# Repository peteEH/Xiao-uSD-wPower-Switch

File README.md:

# Xiao-uSD-wPower-Switch

You should definately purchase a pre-made Adafruit variant: https://www.adafruit.com/product/5683 --- if you don't need a power switch.
- free to select the right p-channel FET that is logic-level compatible, has lower RDSon for the SDcard rail
- hard to beat the Adafruit board for cost... but shipping to Canada is a killer!

ChatGPT Summary of the Schematic PDF:

The document provides a schematic for a microSD (uSD) card adapter with a power switch, specifically designed for use with Xiao or QT Py microcontrollers. It details the electrical components and their configurations, including capacitors, resistors, and a power MOSFET (Q1) for controlling power to the SD card. The schematic includes connections for power, ground, and various data lines (MOSI, MISO, SCLK, CS_N) necessary for SPI communication with the SD card. It also specifies the physical dimensions of the board and the placement of connectors and components, ensuring compatibility with the Xiao or QT Py form factor.

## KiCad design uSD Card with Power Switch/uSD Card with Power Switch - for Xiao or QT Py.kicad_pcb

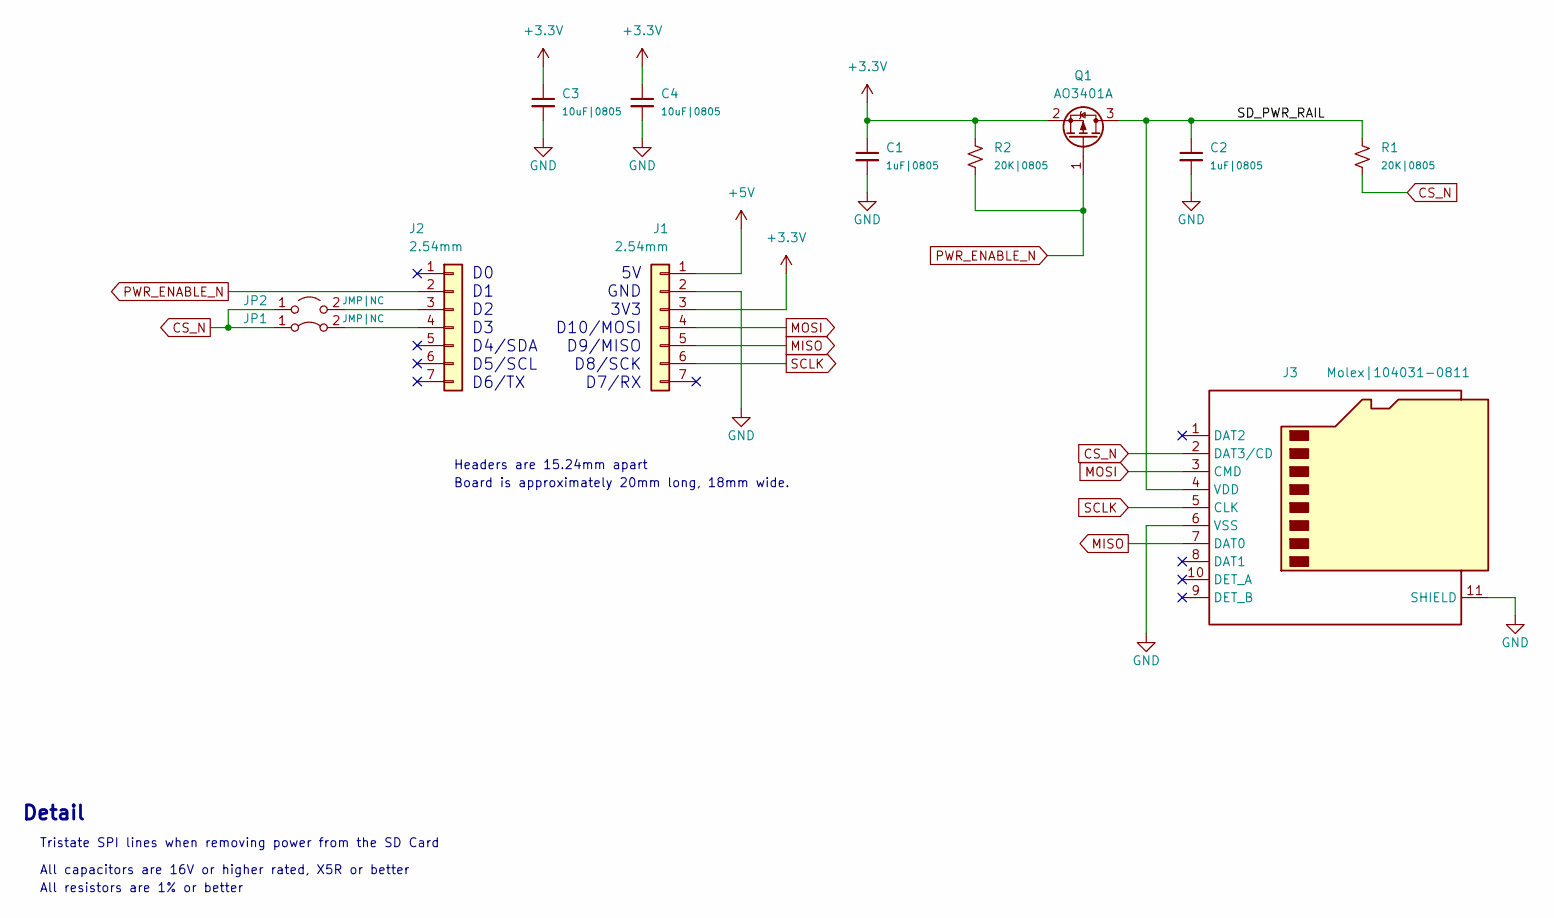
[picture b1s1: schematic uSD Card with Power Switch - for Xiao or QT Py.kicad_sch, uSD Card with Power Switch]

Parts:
C1, C2: 1uF|0805; C_0805_2012Metric
C3, C4: 10uF|0805; C_0805_2012Metric
J1, J2: 2.54mm; PinSocket_1x07_P2.54mm_Vertical
J3: Molex|104031-0811; microSD_HC_Molex_104031-0811
JP1: JMP|NC; SolderJumper-2_P1.3mm_Bridged_RoundedPad1.0x1.5mm
JP2: JMP|NC; SolderJumper-2_P1.3mm_Open_TrianglePad1.0x1.5mm
Q1: AO3401A; SOT-23
R1, R2: 20K|0805; R_0805_2012Metric

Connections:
+3.3V: C1.1, C3.1, C4.1, J1.3, Q1.2 (S), R2.1
+5V: J1.1
/SD_PWR_RAIL: C2.1, J3.4 (VDD), Q1.3 (D), R1.1
CS_N: J3.2 (DAT3/CD), JP1.1 (A), JP2.1 (A), R1.2
GND: C1.2, C2.2, C3.2, C4.2, J1.2, J3.6 (VSS), J3.11 (SHIELD)
MISO: J1.5, J3.7 (DAT0)
MOSI: J1.4, J3.3 (CMD)
unnamed: J2.3, JP2.2 (B)
unnamed: J2.4, JP1.2 (B)
PWR_ENABLE_N: J2.2, Q1.1 (G), R2.2
SCLK: J1.6, J3.5 (CLK)

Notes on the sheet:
D0 D1 D2 D3 D4/SDA D5/SCL D6/TX
Detail
Headers are 15.24mm apart
All resistors are 1% or better
Board is approximately 20mm long, 18mm wide.
All capacitors are 16V or higher rated, X5R or better
5V GND 3V3 D10/MOSI D9/MISO D8/SCK D7/RX
Tristate SPI lines when removing power from the SD Card

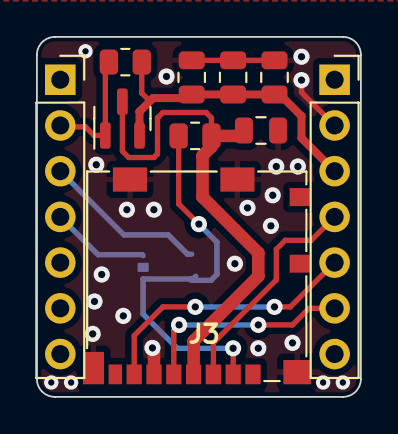
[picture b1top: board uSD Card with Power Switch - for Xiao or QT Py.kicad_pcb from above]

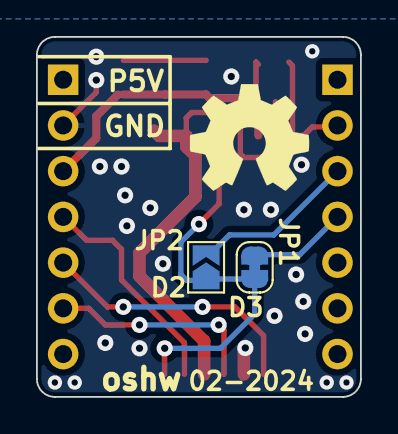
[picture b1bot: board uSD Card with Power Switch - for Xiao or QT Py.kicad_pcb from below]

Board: 2 copper layers, 18.0 x 20.0 mm, 12 parts (2 on the bottom side), 10 nets.

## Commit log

2024-02-17 Update LICENSE
